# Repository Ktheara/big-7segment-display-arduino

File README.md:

# 2.5inch 7segment display arduino

Following [EmSevenSegment](https://github.com/Electromed/EmSevenSegment).

## Circuit
  - HEF4094B:
  - ULN2803:

## Software

Arduino with 2.3inch 7-segment display using shift registers.

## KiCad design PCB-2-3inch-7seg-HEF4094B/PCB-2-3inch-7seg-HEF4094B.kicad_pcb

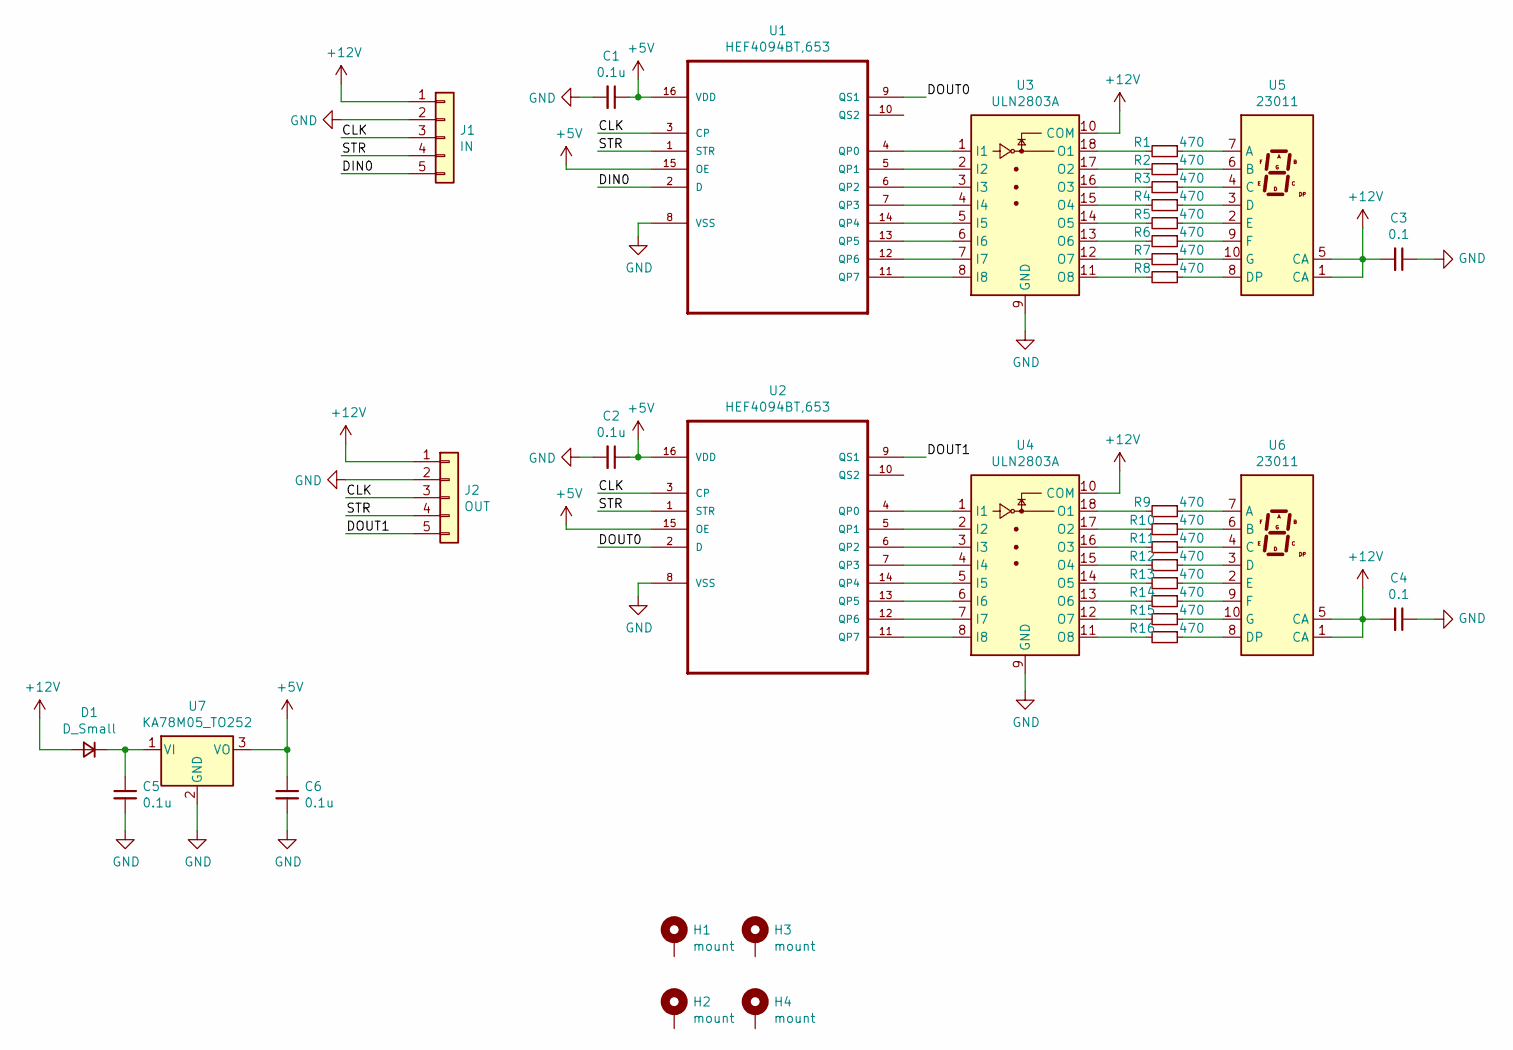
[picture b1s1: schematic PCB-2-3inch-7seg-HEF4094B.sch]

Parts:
C1, C2, C5, C6: 0.1u; C_0805_2012Metric
C3, C4: 0.1; C_0805_2012Metric
D1: D_Small; D_SMA
H1, H2, H3, H4: mount; MountingHole_3.5mm_Pad
J1: IN; PinSocket_1x05_P2.54mm_Vertical
J2: OUT; PinSocket_1x05_P2.54mm_Vertical
R1, R2, R3, R4, R5, R6, R7, R8, R9, R10, R11, R12, R13, R14, R15, R16: 470; R_Axial_DIN0207_L6.3mm_D2.5mm_P10.16mm_Horizontal
U1, U2: HEF4094BT,653; SOIC-16_3.9x9.9mm_P1.27mm
U3, U4: ULN2803A; SOP-18_7x12.5mm_P1.27mm
U5, U6: 23011; 23011-7-segment
U7: KA78M05_TO252; TO-252-2

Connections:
+5V: C1.1, C2.1, C6.1, U1.15 (OE), U1.16 (VDD), U2.15 (OE), U2.16 (VDD), U7.3 (VO)
+12V: C3.2, C4.2, D1.2 (A), J1.1, J2.1, U3.10 (COM), U4.10 (COM), U5.1 (CA), U5.5 (CA), U6.1 (CA), U6.5 (CA)
/CLK: J1.3, J2.3, U1.3 (CP), U2.3 (CP)
/DIN0: J1.5, U1.2 (D)
/DOUT0: U1.9 (QS1), U2.2 (D)
/DOUT1: J2.5, U2.9 (QS1)
/STR: J1.4, J2.4, U1.1 (STR), U2.1 (STR)
GND: C1.2, C2.2, C3.1, C4.1, C5.2, C6.2, J1.2, J2.2, U1.8 (VSS), U2.8 (VSS), U3.9 (GND), U4.9 (GND), U7.2 (GND)
unnamed: C5.1, D1.1 (K), U7.1 (VI)
unnamed: R1.1, U5.7 (A)
unnamed: R1.2, U3.18 (O1)
unnamed: R2.1, U5.6 (B)
unnamed: R2.2, U3.17 (O2)
unnamed: R3.1, U5.4 (C)
unnamed: R3.2, U3.16 (O3)
unnamed: R4.1, U5.3 (D)
unnamed: R4.2, U3.15 (O4)
unnamed: R5.1, U5.2 (E)
unnamed: R5.2, U3.14 (O5)
unnamed: R6.1, U5.9 (F)
unnamed: R6.2, U3.13 (O6)
unnamed: R7.1, U5.10 (G)
unnamed: R7.2, U3.12 (O7)
unnamed: R8.1, U5.8 (DP)
unnamed: R8.2, U3.11 (O8)
unnamed: R9.1, U6.7 (A)
unnamed: R9.2, U4.18 (O1)
unnamed: R10.1, U6.6 (B)
unnamed: R10.2, U4.17 (O2)
unnamed: R11.1, U6.4 (C)
unnamed: R11.2, U4.16 (O3)
unnamed: R12.1, U6.3 (D)
unnamed: R12.2, U4.15 (O4)
unnamed: R13.1, U6.2 (E)
unnamed: R13.2, U4.14 (O5)
unnamed: R14.1, U6.9 (F)
unnamed: R14.2, U4.13 (O6)
unnamed: R15.1, U6.10 (G)
unnamed: R15.2, U4.12 (O7)
unnamed: R16.1, U6.8 (DP)
unnamed: R16.2, U4.11 (O8)
unnamed: U1.4 (QP0), U3.1 (I1)
unnamed: U1.5 (QP1), U3.2 (I2)
unnamed: U1.6 (QP2), U3.3 (I3)
unnamed: U1.7 (QP3), U3.4 (I4)
unnamed: U1.11 (QP7), U3.8 (I8)
unnamed: U1.12 (QP6), U3.7 (I7)
unnamed: U1.13 (QP5), U3.6 (I6)
unnamed: U1.14 (QP4), U3.5 (I5)
unnamed: U2.4 (QP0), U4.1 (I1)
unnamed: U2.5 (QP1), U4.2 (I2)
unnamed: U2.6 (QP2), U4.3 (I3)
unnamed: U2.7 (QP3), U4.4 (I4)
unnamed: U2.11 (QP7), U4.8 (I8)
unnamed: U2.12 (QP6), U4.7 (I7)
unnamed: U2.13 (QP5), U4.6 (I6)
unnamed: U2.14 (QP4), U4.5 (I5)

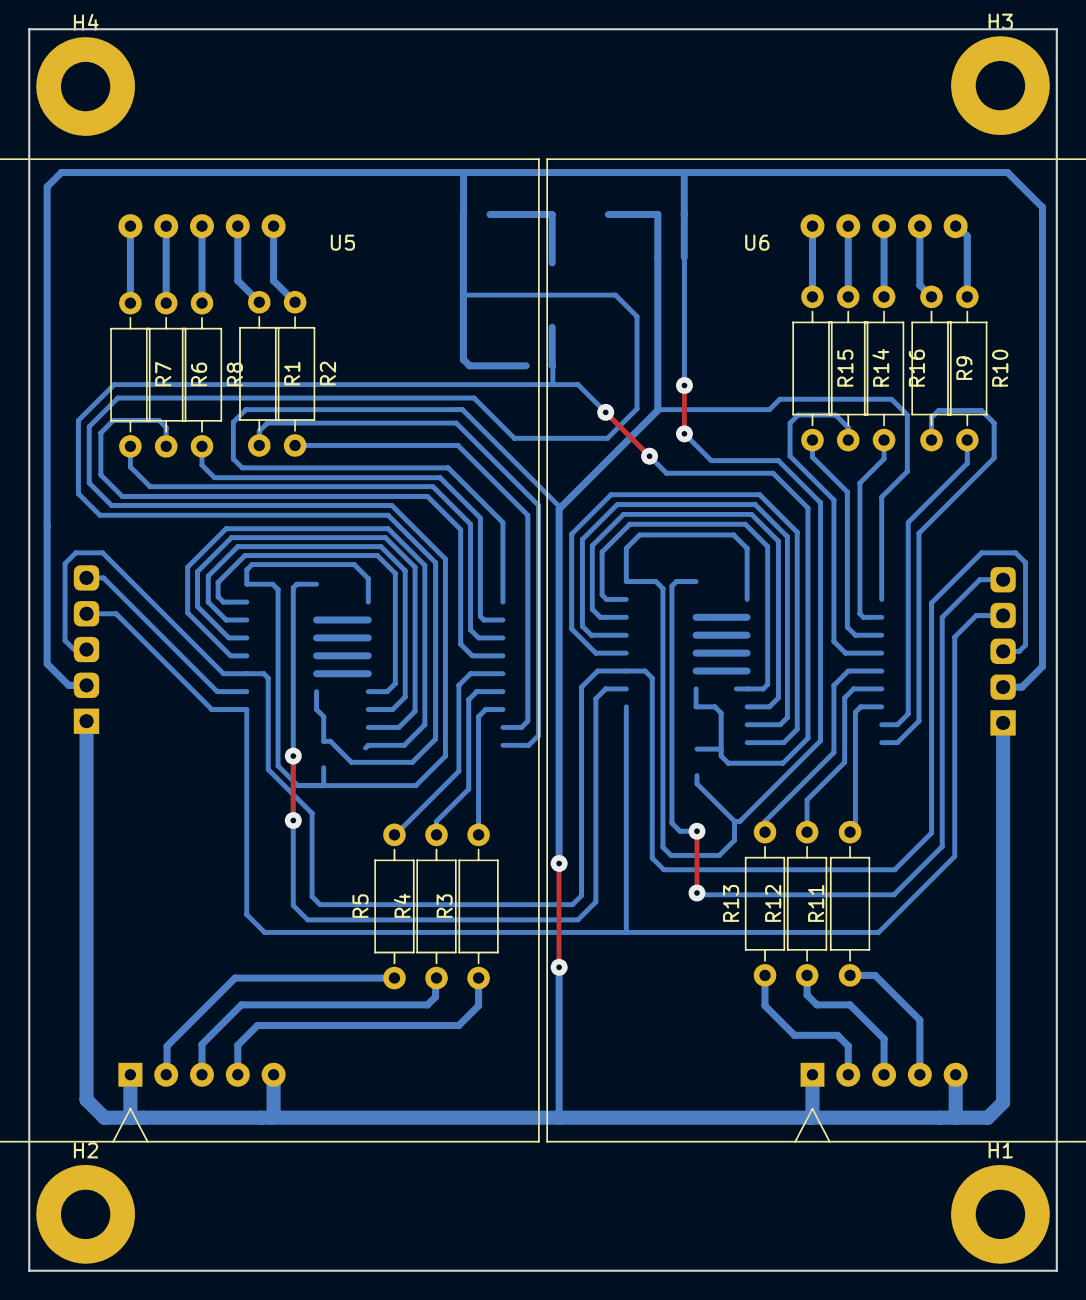
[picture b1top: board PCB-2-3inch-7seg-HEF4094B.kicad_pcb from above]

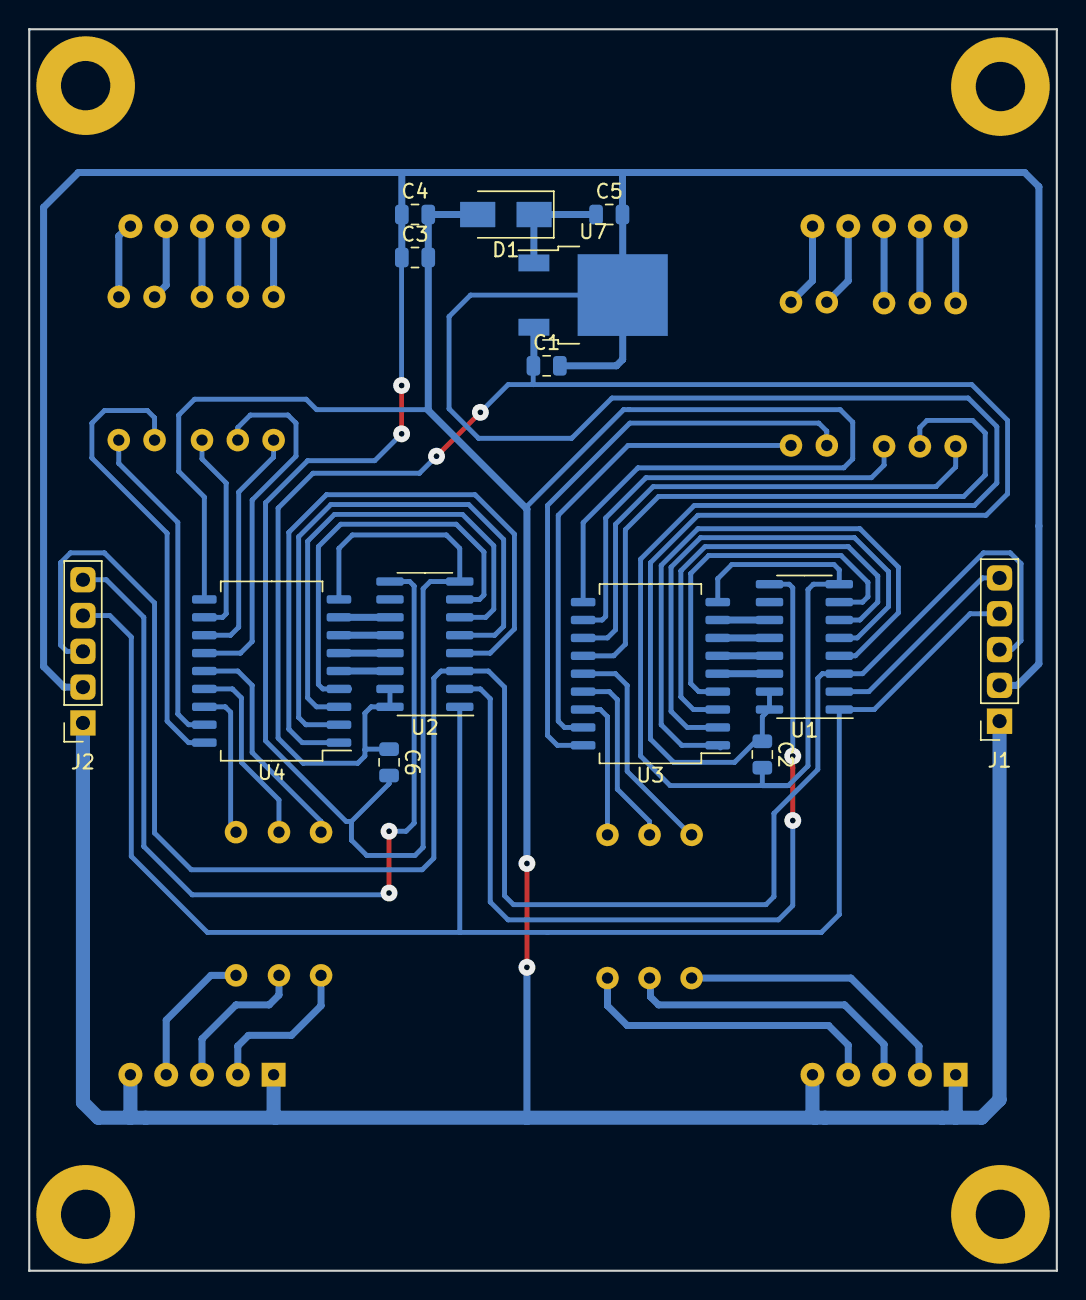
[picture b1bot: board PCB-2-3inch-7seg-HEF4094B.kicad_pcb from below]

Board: 2 copper layers, 72.9 x 88.1 mm, 36 parts (14 on the bottom side), 57 nets.

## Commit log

2020-08-04 add pcb files
2020-08-04 finalize sch
2020-08-05 finalize pcb v1.0
2020-08-06 DIY print
2020-08-07 added arduino code
2020-08-07 update credit.
2020-08-26 test-work-well
